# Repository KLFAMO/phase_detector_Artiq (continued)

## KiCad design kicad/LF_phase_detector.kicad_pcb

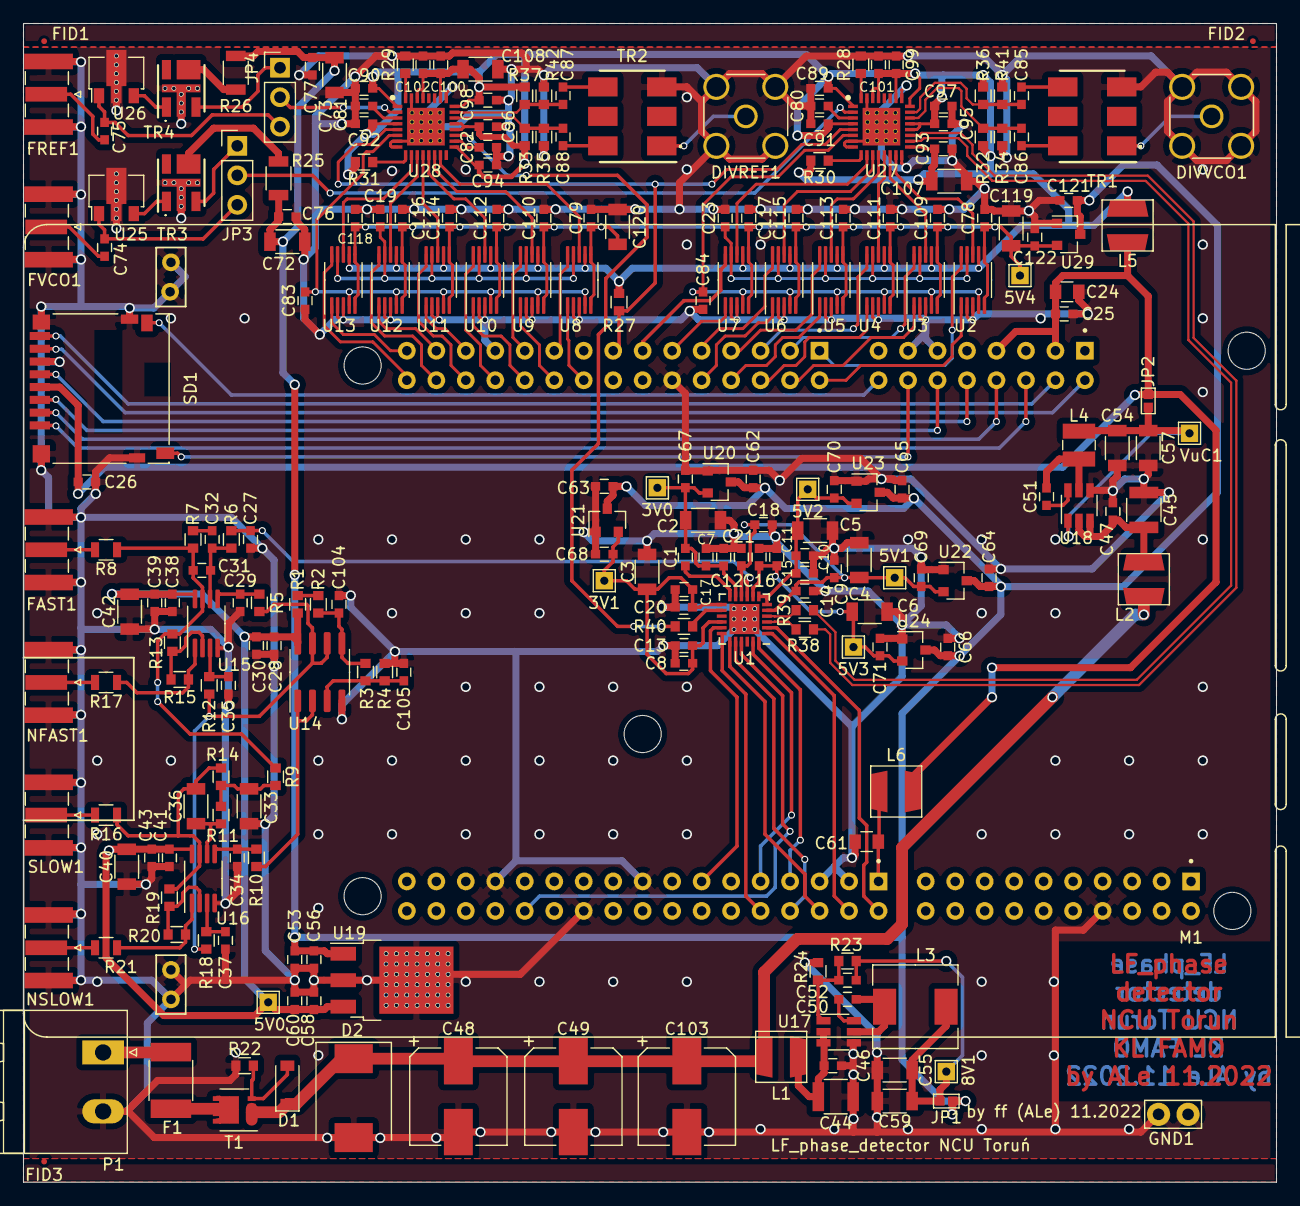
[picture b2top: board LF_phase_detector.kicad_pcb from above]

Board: 2 copper layers, 108.0 x 99.8 mm, 233 parts (0 on the bottom side), 143 nets.

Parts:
3V0, 3V1, 5V0, 5V1, 5V2, 5V3, 5V4, 8V1: TestPoint; Test_Point_THTPad_1.5x1.5mm_Drill0.7mm
C1, C12, C13, C14, C15, C16, C20, C21, C80, C81, C82: 1n 50V C0G; C_0603
C2, C3, C4, C5, C6, C40, C42, C72, C73, C107, C108, C119, C120: 10uF 25V X5R; C_1206
C7, C8, C9, C10, C11, C17, C18, C19, C23, C25, C26, C30, C39, C43, C46, C47, C50, C51, C56, C58, C76, C77, C78, C79, C83, C84, C89, C90, C91, C92, C93, C94, C95, C96, C97, C98, C99, C100, C101, C102, C109, C110, C111, C112, C113, C114, C115, C116, C117, C118: 100n 50V X7R; C_0603
C24, C61: GRM21BR71A106KE51L; C_0805
C27: 470p 50V C0G; C_0603
C28, C38, C41: 100p 50V C0G; C_0603
C29, C32, C34, C35, C37, C74, C75, C85, C86, C87, C88, C104, C105: 10n 50V C0G; C_0603
C31: DNP; C_0603
C33: 100n 50V C0G; C_1206
C36: 20n 50V C0G; C_1206
C44, C45: GRM32ER71H106KA12L; C_1210
C48, C49, C103: EXV107M035A9MAA; CP_Elec_8x10.5
C52: 82p 50V C0G; C_0603
C53, C60, C62, C63, C64, C65, C66, C67, C68, C69, C70, C71, C121, C122: 4u7 10V X5R; C_0603
C54, C55, C57, C59: GRM31CR71A226KE15L; C_1206
D1: BZT52C15; D_SOD-123
D2: SMAJ24A; D_SMC
DIVREF1: SMA6251A1-3GT50G-50; SMA_Amphenol_132291-12_Vertical
DIVVCO1: SMA6251A1-3GT50G-50; SMA_Amphenol_132291-12_Vertical
F1: 0ZCG0110CF2B; R_1812
FAST1: RF2-145A-T-17-50-G-HDW; SMA_Samtec_SMA-J-P-X-ST-EM1_EdgeMount
FID1, FID2, FID3: PAD; Fiducial_0.5mm_Dia_1mm_Outer
FREF1: RF2-145A-T-17-50-G-HDW; SMA_Samtec_SMA-J-P-X-ST-EM1_EdgeMount
FVCO1: RF2-145A-T-17-50-G-HDW; SMA_Samtec_SMA-J-P-X-ST-EM1_EdgeMount
GND1: TestPoint; Test_Point_Bridge_Pitch2.54mm_Drill1.0mm
JP1, JP2: Jumper_NO_Small; GS2_small
JP3, JP4: igły 3x1x2,54mm; Pin_Header_Straight_1x03_Pitch2.54mm
L1, L2: LQH44PH220MPRL; L_MURATA_LQH44
L3: 74477710; L_Wuerth_HCM-7050
L4: SRP3212-3R3M; L_Bourns_SRP3212
L5, L6: LQH44PN330MPRL; L_MURATA_LQH44
M1: NUCLEO-H743ZI; MODULE_NUCLEO-F746ZG_mini_M
NFAST1: RF2-145A-T-17-50-G-HDW; SMA_Samtec_SMA-J-P-X-ST-EM1_EdgeMount
NSLOW1: RF2-145A-T-17-50-G-HDW; SMA_Samtec_SMA-J-P-X-ST-EM1_EdgeMount
P1: MSTBA 2,5/ 2-G-5,08 - 1757242; PhoenixContact_MSTBA-G_02x5.08mm_Angled
R1, R2, R3, R4, R5, R10, R12, R13, R15, R18, R19, R20, R27, R30, R31: 10k 1%; R_0603_ff
R6, R7: 150R 1%; R_0603_ff
R8, R16, R17, R21: 49,9R 1%; R_0805
R9, R14: 1k 1%; R_0603_ff
R11: 2,26k 1%; R_0603_ff
R22: 4,7k; R_0603_ff
R23: 180k 1%; R_0603_ff
R24: 20k 1%; R_0603_ff
R25, R26: 133R 1%; R_1206
R28, R29: 4,12k 1%; R_0603_ff
R32, R33, R36, R37: 127R 1%; R_0603_ff
R34, R35, R41, R42: 83R 1%; R_0603_ff
R38, R39, R40: 24,9R 1%; R_0603_ff
SD1: DM3D-SF; Hirose_DM3D-SF
SLOW1: RF2-145A-T-17-50-G-HDW; SMA_Samtec_SMA-J-P-X-ST-EM1_EdgeMount
T1: AO4485; Diodes_PowerDI3333-8
TR1, TR2: ADT2-1T+; ADT21T1P
TR3, TR4: TCBT-14+; TCBT14
U1: HMC984LP4E; QFN-24_4x4mm_Pitch0.5mm_NoMask
U2, U3, U4, U5, U6, U7, U8, U9, U10, U11, U12, U13: TMUX1204DGSR; VSSOP-10_3x3mm_P0.5mm
U14: OPA2325; SOIC-8_3.9x4.9mm_P1.27mm
U15, U16: ADA4807-2ARM; MSOP-8_3x3mm_P0.65mm
U17: AP63200WU; TSOT-23-6
U18: AP63203WU-7; TSOT-23-6
U19: L78M05ACDT; TO-252-3_TabPin2
U20, U21: AP2210N-3.0TRG1; SOT-23
U22, U23, U24, U29: AP2210N-5.0TRG1; SOT-23
U25, U26: GALI-39+; SOT-89-3
U27, U28: AD9515BCPZ; QFN-32-1EP_5x5mm_Pitch0.5mm_ThermalVias
VuC1: TestPoint; Test_Point_THTPad_1.5x1.5mm_Drill0.7mm

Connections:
+3V3: C89.1, C90.1, C91.1, C92.1, C93.1, C94.1, C95.1, C96.1, C97.1, C98.1, C99.1, C100.1, C101.1, C102.1, C107.1, C108.1, L5.1, R27.2, R30.2, R31.2, R32.2, R33.2, R36.2, R37.2, U2.7, U3.7, U4.7, U5.7, U6.7, U7.7, U8.7, U9.7, U10.7, U11.7, U12.7, U13.7, U27.1, U27.4, U27.17, U27.20, U27.21, U27.24, U27.26, U27.29, U27.30, U28.1, U28.4, U28.17, U28.20, U28.21, U28.24, U28.26, U28.29, U28.30
+5V: 5V4.1, C78.1, C79.1, C109.1, C110.1, C111.1, C112.1, C113.1, C114.1, C115.1, C116.1, C117.1, C118.1, C119.1, C120.1, C122.1, U2.5, U2.6, U3.5, U3.6, U4.5, U4.6, U5.5, U5.6, U6.5, U6.6, U7.5, U7.6, U8.5, U8.6, U9.5, U9.6, U10.5, U10.6, U11.5, U11.6, U12.5, U12.6, U13.5, U13.6, U29.2
+5VA: 5V0.1, C28.1, C30.1, C38.1, C39.1, C40.2, C41.1, C42.1, C43.1, C58.2, C60.1, R1.2, U14.8, U15.8, U16.8, U19.3
+8V: C53.1, C56.2, C62.1, C63.1, C64.1, C65.1, C66.1, C72.1, C73.1, C76.1, C77.1, C121.1, JP1.2, R25.1, R26.1, U19.1, U20.3, U21.3, U22.3, U23.3, U24.3, U29.3
+15V: C48.1, C49.1, C103.1, D1.1, D2.1, L1.2, L2.2, T1.1, T1.2, T1.3
/Inputs and prescaler/DIV10+: C85.1, R36.1, R41.1, U27.23
/Inputs and prescaler/DIV10-: C86.1, R32.1, R34.1, U27.22
/Inputs and prescaler/DIV11+: R38.1, U27.19
/Inputs and prescaler/DIV11-: R39.1, U27.18
/Inputs and prescaler/DIV20+: C87.1, R37.1, R42.1, U28.23
/Inputs and prescaler/DIV20-: C88.1, R33.1, R35.1, U28.22
/Loop filter and outputs/VHALF: R5.1, R12.1, R18.1, U14.6, U14.7
/Loop filter and outputs/VQUOTER: R10.1, U14.1, U14.2
/Microcontroller F030/AS1_2: M1.CN9_2, U2.1
/Microcontroller F030/AS1_3: M1.CN9_4, U3.1
/Microcontroller F030/AS1_4: M1.CN9_6, U4.1
/Microcontroller F030/AS1_5: M1.CN9_8, U5.1
/Microcontroller F030/AS1_6: M1.CN9_10, U6.1
/Microcontroller F030/AS1_7: M1.CN9_11, U7.1
/Microcontroller F030/AS2_2: M1.CN9_18, U8.1
/Microcontroller F030/AS2_3: M1.CN9_20, U9.1
/Microcontroller F030/AS2_4: M1.CN9_22, U10.1
/Microcontroller F030/AS2_5: M1.CN9_25, U11.1
/Microcontroller F030/AS2_6: M1.CN9_27, U12.1
/Microcontroller F030/AS2_7: M1.CN9_29, U13.1
/Microcontroller F030/BS1_2: M1.CN9_1, U2.10
/Microcontroller F030/BS1_3: M1.CN9_3, U3.10
/Microcontroller F030/BS1_4: M1.CN9_5, U4.10
/Microcontroller F030/BS1_5: M1.CN9_7, U5.10
/Microcontroller F030/BS1_6: M1.CN9_9, U6.10
/Microcontroller F030/BS1_7: M1.CN9_13, U7.10
/Microcontroller F030/BS2_2: M1.CN9_19, U8.10
/Microcontroller F030/BS2_3: M1.CN9_21, U9.10
/Microcontroller F030/BS2_4: M1.CN9_24, U10.10
/Microcontroller F030/BS2_5: M1.CN9_26, U11.10
/Microcontroller F030/BS2_6: M1.CN9_28, U12.10
/Microcontroller F030/BS2_7: M1.CN9_30, U13.10
/Microcontroller F030/REF1_1:3: C23.1, U2.9, U3.9, U4.9, U5.9, U6.9, U7.9
/Microcontroller F030/REF2_1:3: C19.1, U8.9, U9.9, U10.9, U11.9, U12.9, U13.9
/Microcontroller F030/uC feed and SDcard/SD_CK: M1.CN8_10, SD1.5
/Microcontroller F030/uC feed and SDcard/SD_CMD: M1.CN8_12, SD1.3
/Microcontroller F030/uC feed and SDcard/SD_D0: M1.CN8_2, SD1.7
/Microcontroller F030/uC feed and SDcard/SD_D1: M1.CN8_4, SD1.8
/Microcontroller F030/uC feed and SDcard/SD_D2: M1.CN8_6, SD1.1
/Microcontroller F030/uC feed and SDcard/SD_D3: M1.CN8_8, SD1.2
/Microcontroller F030/uC feed and SDcard/SD_DET1: M1.CN8_16, SD1.9
/Microcontroller F030/uC feed and SDcard/SD_DET2: M1.CN8_14, SD1.10
AVDD: 3V0.1, C1.2, C2.1, C7.1, C12.1, C67.1, U1.11, U20.2
CEN: M1.CN10_13, U1.17
CP: C27.2, R6.2, U1.9
DIV1+: R38.2, U1.3
DIV1-: R39.2, U1.4
DIV2: R40.2, U1.14
DNSAT: M1.CN10_7, U1.24
DVDD: 3V1.1, C3.1, C8.1, C13.1, C17.1, C20.1, C68.1, U1.13, U1.16, U21.2
GND: C2.2, C3.2, C4.2, C5.2, C6.2, C7.2, C8.2, C9.2, C10.2, C11.2, C12.2, C13.2, C14.2, C15.2, C16.2, C17.2, C18.2, C19.2, C20.2, C21.2, C23.2, C24.2, C25.2, C26.2, C27.1, C28.2, C29.2, C30.2, C33.2, C34.2, C35.2, C37.2, C38.2, C39.2, C40.1, C41.2, C42.2, C43.2, C44.2, C45.2, C46.2, C47.2, C48.2, C49.2, C53.2, C54.2, C55.2, C56.1, C57.2, C58.1, C59.2, C60.2, C61.2, C62.2, C63.2, C64.2, C65.2, C66.2, C67.2, C68.2, C69.2, C70.2, C71.2, C72.2, C73.2, C76.2, C77.2, C78.2, C79.2, C80.1, C81.1, C82.1, C83.2, C84.2, C89.2, C90.2, C91.2, C92.2, C93.2, C94.2, C95.2, C96.2, C97.2, C98.2, C99.2, C100.2, C101.2, C102.2, C103.2, C104.2, C105.2, C107.2, C108.2, C109.2, C110.2, C111.2, C112.2, C113.2, C114.2, C115.2, C116.2, C117.2, C118.2, C119.2, C120.2, C121.2, C122.2, D2.2, DIVREF1.2, DIVVCO1.2, FAST1.2, FREF1.2, FVCO1.2, GND1.1, M1.35, M1.CN7_8, M1.CN8_11, M1.CN8_13, M1.CN9_12, M1.CN9_23, M1.CN10_3, M1.CN10_5, M1.CN10_17, M1.CN10_22, M1.CN10_27, NFAST1.2, NSLOW1.2, P1.2, R4.1, R22.1, R24.2, R28.2, R29.2, R34.2, R35.2, R41.2, R42.2, SD1.6, SD1.11, SLOW1.2, TR1.3, TR2.3, TR3.5, TR4.5, U1.25, U2.2, U2.3, U3.2, U3.3, U4.2, U4.3, U5.2, U5.3, U6.2, U6.3, U7.2, U7.3, U8.2, U8.3, U9.2, U9.3, U10.2, U10.3, U11.2, U11.3, U12.2, U12.3, U13.2, U13.3, U14.4, U15.4, U16.4, U17.4, U18.4, U19.2, U20.1, U21.1, U22.1, U23.1, U24.1, U25.2, U26.2, U27.7, U27.8, U27.16, U27.25, U27.31, U27.33, U28.7, U28.8, U28.25, U28.31, U28.33, U29.1
LD-D0: M1.CN10_2, U1.2
MISO: M1.CN10_10, U1.18
MOSI: M1.CN10_8, U1.20
NSS: M1.CN10_6, U1.19
unnamed: 8V1.1, C52.1, C55.1, C59.1, JP1.1, L3.1, R23.1
unnamed: C1.1, U1.12
unnamed: C29.1, R5.2, U15.5
unnamed: C31.1, C32.1, R6.1, U15.6
unnamed: C31.2, R7.1, R8.1, R9.1, R13.1, U15.7
unnamed: C32.2, R7.2
unnamed: C33.1, R9.2, R11.2, R14.1
unnamed: C34.1, R10.2, U16.5
unnamed: C35.1, R12.2, U15.3
unnamed: C36.1, R11.1, U16.6
unnamed: C36.2, R14.2, R16.1, R19.1, U16.7
unnamed: C37.1, R18.2, U16.3
unnamed: C44.1, C46.1, L1.1, U17.2, U17.3
unnamed: C45.1, C47.1, L2.1, U18.2, U18.3
unnamed: C50.1, L3.2, U17.5
unnamed: C50.2, U17.6
unnamed: C51.1, L4.2, U18.5
unnamed: C51.2, U18.6
unnamed: C52.2, R23.2, R24.1, U17.1
unnamed: C54.1, C57.1, JP2.2, L4.1, U18.1, VuC1.1
unnamed: C74.1, JP3.3, U25.1
unnamed: C74.2, FVCO1.1
unnamed: C75.1, JP4.3, U26.1
unnamed: C75.2, FREF1.1
unnamed: C80.2, U27.3
unnamed: C81.2, U28.3
unnamed: C82.2, U28.18
unnamed: C85.2, TR1.4
unnamed: C86.2, TR1.6
unnamed: C87.2, TR2.4
unnamed: C88.2, TR2.6
unnamed: C104.1, R2.1, R3.2, U14.5
unnamed: C105.1, R3.1, R4.2, U14.3
unnamed: D1.2, R22.2, T1.4
unnamed: DIVREF1.1, TR2.1
unnamed: DIVVCO1.1, TR1.1
unnamed: F1.1, T1.5
unnamed: F1.2, P1.1
unnamed: FAST1.1, R8.2
unnamed: JP3.1, TR3.2
unnamed: JP3.2, U27.2
unnamed: JP4.1, TR4.2
unnamed: JP4.2, U28.2
unnamed: NFAST1.1, R17.2
unnamed: NSLOW1.1, R21.2
unnamed: R1.1, R2.2
unnamed: R13.2, R15.1, U15.2
unnamed: R15.2, R17.1, U15.1
unnamed: R16.2, SLOW1.1
unnamed: R19.2, R20.1, U16.2
unnamed: R20.2, R21.1, U16.1
unnamed: R25.2, TR3.3
unnamed: R26.2, TR4.3
unnamed: R28.1, U27.32
unnamed: R29.1, U28.32
unnamed: R30.1, U27.9
unnamed: R31.1, U28.9
unnamed: R40.1, U28.19
unnamed: TR3.1, U25.3
unnamed: TR4.1, U26.3
REF123: C84.1, U2.4, U3.4, U4.4, U5.4, U6.4, U7.4, U27.6
REF223: C83.1, U8.4, U9.4, U10.4, U11.4, U12.4, U13.4, U28.6
REFEN: M1.CN10_4, U1.1
S1_2: U2.8, U27.15
S1_3: U3.8, U27.14
S1_4: U4.8, U27.13
S1_5: U5.8, U27.12
S1_6: U6.8, U27.11
S1_7: U7.8, U27.10
S2_2: U8.8, U28.15
S2_3: U9.8, U28.14
S2_4: U10.8, U28.13
S2_5: U11.8, U28.12
S2_6: U12.8, U28.11
S2_7: U13.8, U28.10
SCK: M1.CN10_26, U1.21
SYNCB: M1.CN9_15, R27.1, U27.5, U28.5
UPSAT: M1.CN10_9, U1.23
VAREF: C61.1, L6.1, M1.CN10_1
VCCPD: 5V1.1, C4.1, C9.1, C14.1, C18.1, C21.1, C69.1, U1.5, U1.10, U22.2
VDDCP: 5V3.1, C6.1, C11.1, C16.1, C71.1, U1.8, U24.2
VDDPD: 5V2.1, C5.1, C10.1, C15.1, C70.1, U1.6, U1.7, U23.2
VuC: C24.1, C25.1, C26.1, JP2.1, L5.2, L6.2, M1.CN8_3, M1.CN8_7, SD1.4

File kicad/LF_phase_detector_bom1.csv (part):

"Source:","D:\Projekty\FAMO\LF_phase_detector\LF_phase_detector.sch"
"Date:","24.11.2022 08:50:30"
"Tool:","Eeschema (5.1.12)-1"
"Generator:","C:\Program Files\KiCad\bin\scripting\plugins/bom_csv_grouped_by_value.py"
"Component Count:","233"

"Individual Components:"

"Item","Qty","Reference(s)","Value","LibPart","Footprint","Datasheet","Comm","Vendor"
"","","3V0","TestPoint","Connector:TestPoint","Connectors_TestPoints:Test_Point_THTPad_1.5x1.5mm_Drill0.7mm","~","",""
"","","3V1","TestPoint","Connector:TestPoint","Connectors_TestPoints:Test_Point_THTPad_1.5x1.5mm_Drill0.7mm","~","",""
"","","5V0","TestPoint","Connector:TestPoint","Connectors_TestPoints:Test_Point_THTPad_1.5x1.5mm_Drill0.7mm","~","",""
"","","5V1","TestPoint","Connector:TestPoint","Connectors_TestPoints:Test_Point_THTPad_1.5x1.5mm_Drill0.7mm","~","",""
"","","5V2","TestPoint","Connector:TestPoint","Connectors_TestPoints:Test_Point_THTPad_1.5x1.5mm_Drill0.7mm","~","",""
"","","5V3","TestPoint","Connector:TestPoint","Connectors_TestPoints:Test_Point_THTPad_1.5x1.5mm_Drill0.7mm","~","",""
"","","5V4","TestPoint","Connector:TestPoint","Connectors_TestPoints:Test_Point_THTPad_1.5x1.5mm_Drill0.7mm","~","",""
"","","8V1","TestPoint","Connector:TestPoint","Connectors_TestPoints:Test_Point_THTPad_1.5x1.5mm_Drill0.7mm","~","",""
"","","C1","1n 50V C0G","Device:C","Capacitors_SMD:C_0603","~","",""
"","","C2","10uF 25V X5R","Device:C","Capacitors_SMD:C_1206","~","",""
"","","C3","10uF 25V X5R","Device:C","Capacitors_SMD:C_1206","~","",""
"","","C4","10uF 25V X5R","Device:C","Capacitors_SMD:C_1206","~","",""
"","","C5","10uF 25V X5R","Device:C","Capacitors_SMD:C_1206","~","",""
"","","C6","10uF 25V X5R","Device:C","Capacitors_SMD:C_1206","~","",""
"","","C7","100n 50V X7R","Device:C","Capacitors_SMD:C_0603","~","",""
"","","C8","100n 50V X7R","Device:C","Capacitors_SMD:C_0603","~","",""
"","","C9","100n 50V X7R","Device:C","Capacitors_SMD:C_0603","~","",""
"","","C10","100n 50V X7R","Device:C","Capacitors_SMD:C_0603","~","",""
"","","C11","100n 50V X7R","Device:C","Capacitors_SMD:C_0603","~","",""
"","","C12","1n 50V C0G","Device:C","Capacitors_SMD:C_0603","~","",""
"","","C13","1n 50V C0G","Device:C","Capacitors_SMD:C_0603","~","",""
"","","C14","1n 50V C0G","Device:C","Capacitors_SMD:C_0603","~","",""
"","","C15","1n 50V C0G","Device:C","Capacitors_SMD:C_0603","~","",""
"","","C16","1n 50V C0G","Device:C","Capacitors_SMD:C_0603","~","",""
"","","C17","100n 50V X7R","Device:C","Capacitors_SMD:C_0603","~","",""
"","","C18","100n 50V X7R","Device:C","Capacitors_SMD:C_0603","~","",""
"","","C19","100n 50V X7R","Device:C","Capacitors_SMD:C_0603","~","",""
"","","C20","1n 50V C0G","Device:C","Capacitors_SMD:C_0603","~","",""
"","","C21","1n 50V C0G","Device:C","Capacitors_SMD:C_0603","~","",""
"","","C23","100n 50V X7R","Device:C","Capacitors_SMD:C_0603","~","",""
"","","C24","10u X7R 50V","Device:C","Capacitors_SMD:C_1210","~","",""
"","","C25","100n X7R 50V","Device:C","Capacitors_SMD:C_0603","~","",""
"","","C26","100n X7R 50V","Device:C","Capacitors_SMD:C_0603","~","",""
"","","C27","470p 50V C0G","Device:C","Capacitors_SMD:C_0603","~","",""
"","","C28","100p 50V C0G","Device:C","Capacitors_SMD:C_0603","~","",""
"","","C29","10n 50V C0G","Device:C","Capacitors_SMD:C_0603","~","",""
"","","C30","100n 50V X7R","Device:C","Capacitors_SMD:C_0603","~","",""
"","","C31","DNP","Device:C","Capacitors_SMD:C_0603","~","(470p 50V C0G)",""
"","","C32","10n 50V C0G","Device:C","Capacitors_SMD:C_0603","~","",""
"","","C33","100n 50V C0G","Device:C","Capacitors_SMD:C_1206","~","",""
"","","C34","10n 50V C0G","Device:C","Capacitors_SMD:C_0603","~","",""
"","","C35","10n 50V C0G","Device:C","Capacitors_SMD:C_0603","~","",""
"","","C36","20n 50V C0G","Device:C","Capacitors_SMD:C_1206","~","",""
"","","C37","10n 50V C0G","Device:C","Capacitors_SMD:C_0603","~","",""
"","","C38","100p 50V C0G","Device:C","Capacitors_SMD:C_0603","~","",""
"","","C39","100n 50V X7R","Device:C","Capacitors_SMD:C_0603","~","",""
"","","C40","10uF 25V X5R","Device:C","Capacitors_SMD:C_1206","~","",""
"","","C41","100p 50V C0G","Device:C","Capacitors_SMD:C_0603","~","",""
"","","C42","10uF 25V X5R","Device:C","Capacitors_SMD:C_1206","~","",""
"","","C43","100n 50V X7R","Device:C","Capacitors_SMD:C_0603","~","",""
"","","C44","GRM32ER71H106KA12L","Device:C","Capacitors_SMD:C_1210","~","10u 50V X7R Murata",""
"","","C45","GRM32ER71H106KA12L","Device:C","Capacitors_SMD:C_1210","~","10u 50V X7R Murata",""
"","","C46","100n 50V X7R","Device:C","Capacitors_SMD:C_0603","~","",""
"","","C47","100n 50V X7R","Device:C","Capacitors_SMD:C_0603","~","",""
"","","C48","EXV107M035A9MAA","Device:CP","Capacitors_SMD:CP_Elec_8x10.5","~","≥100u ≥30V ≥4000h Ø8 ≥105°C ",""
"","","C49","EXV107M035A9MAA","Device:CP","Capacitors_SMD:CP_Elec_8x10.5","~","≥100u ≥30V ≥4000h Ø8 ≥105°C ",""
"","","C50","100n 50V X7R","Device:C","Capacitors_SMD:C_0603","~","",""
"","","C51","100n 50V X7R","Device:C","Capacitors_SMD:C_0603","~","",""
"","","C52","82p 50V C0G","Device:C","Capacitors_SMD:C_0603","~","",""
"","","C53","4u7 X5R 10V","Device:C","Capacitors_SMD:C_0603","~","",""
"","","C54","GRM31CR71A226KE15L","Device:C","Capacitors_SMD:C_1206","~","22u 10V X7R Murata",""
"","","C55","GRM31CR71A226KE15L","Device:C","Capacitors_SMD:C_1206","~","22u 10V X7R Murata",""
"","","C56","100n 50V X7R","Device:C","Capacitors_SMD:C_0603","~","",""
"","","C57","GRM31CR71A226KE15L","Device:C","Capacitors_SMD:C_1206","~","22u 10V X7R Murata",""
"","","C58","100n 50V X7R","Device:C","Capacitors_SMD:C_0603","~","",""
"","","C59","GRM31CR71A226KE15L","Device:C","Capacitors_SMD:C_1206","~","22u 10V X7R Murata",""
"","","C60","4u7 X5R 10V","Device:C","Capacitors_SMD:C_0603","~","",""
"","","C61","GRM21BR71A106KE51L","Device:C","Capacitors_SMD:C_0805","~","10u 10V X7R",""
"","","C62","4u7 X5R 10V","Device:C","Capacitors_SMD:C_0603","~","",""
"","","C63","4u7 X5R 10V","Device:C","Capacitors_SMD:C_0603","~","",""
"","","C64","4u7 X5R 10V","Device:C","Capacitors_SMD:C_0603","~","",""
"","","C65","4u7 X5R 10V","Device:C","Capacitors_SMD:C_0603","~","",""
"","","C66","4u7 X5R 10V","Device:C","Capacitors_SMD:C_0603","~","",""
"","","C67","4u7 X5R 10V","Device:C","Capacitors_SMD:C_0603","~","",""
"","","C68","4u7 X5R 10V","Device:C","Capacitors_SMD:C_0603","~","",""
"","","C69","4u7 X5R 10V","Device:C","Capacitors_SMD:C_0603","~","",""
"","","C70","4u7 X5R 10V","Device:C","Capacitors_SMD:C_0603","~","",""
"","","C71","4u7 X5R 10V","Device:C","Capacitors_SMD:C_0603","~","",""
"","","C72","10uF 25V X5R","Device:C","Capacitors_SMD:C_1206","~","",""
"","","C73","10uF 25V X5R","Device:C","Capacitors_SMD:C_1206","~","",""
"","","C74","10n 50V C0G","Device:C","Capacitors_SMD:C_0603","~","",""
"","","C75","10n 50V C0G","Device:C","Capacitors_SMD:C_0603","~","",""
"","","C76","100n 50V X7R","Device:C","Capacitors_SMD:C_0603","~","",""
"","","C77","100n 50V X7R","Device:C","Capacitors_SMD:C_0603","~","",""
"","","C78","100n 50V X7R","Device:C","Capacitors_SMD:C_0603","~","",""
"","","C79","100n 50V X7R","Device:C","Capacitors_SMD:C_0603","~","",""
"","","C80","1n 50V C0G","Device:C","Capacitors_SMD:C_0603","~","",""
"","","C81","1n 50V C0G","Device:C","Capacitors_SMD:C_0603","~","",""
"","","C82","1n 50V C0G","Device:C","Capacitors_SMD:C_0603","~","",""
"","","C83","100n 50V X7R","Device:C","Capacitors_SMD:C_0603","~","",""
"","","C84","100n 50V X7R","Device:C","Capacitors_SMD:C_0603","~","",""
"","","C85","10n 50V C0G","Device:C","Capacitors_SMD:C_0603","~","",""
"","","C86","10n 50V C0G","Device:C","Capacitors_SMD:C_0603","~","",""
"","","C87","10n 50V C0G","Device:C","Capacitors_SMD:C_0603","~","",""
"","","C88","10n 50V C0G","Device:C","Capacitors_SMD:C_0603","~","",""
"","","C89","100n 50V X7R","Device:C","Capacitors_SMD:C_0603","~","",""
"","","C90","100n 50V X7R","Device:C","Capacitors_SMD:C_0603","~","",""
"","","C91","100n 50V X7R","Device:C","Capacitors_SMD:C_0603","~","",""
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
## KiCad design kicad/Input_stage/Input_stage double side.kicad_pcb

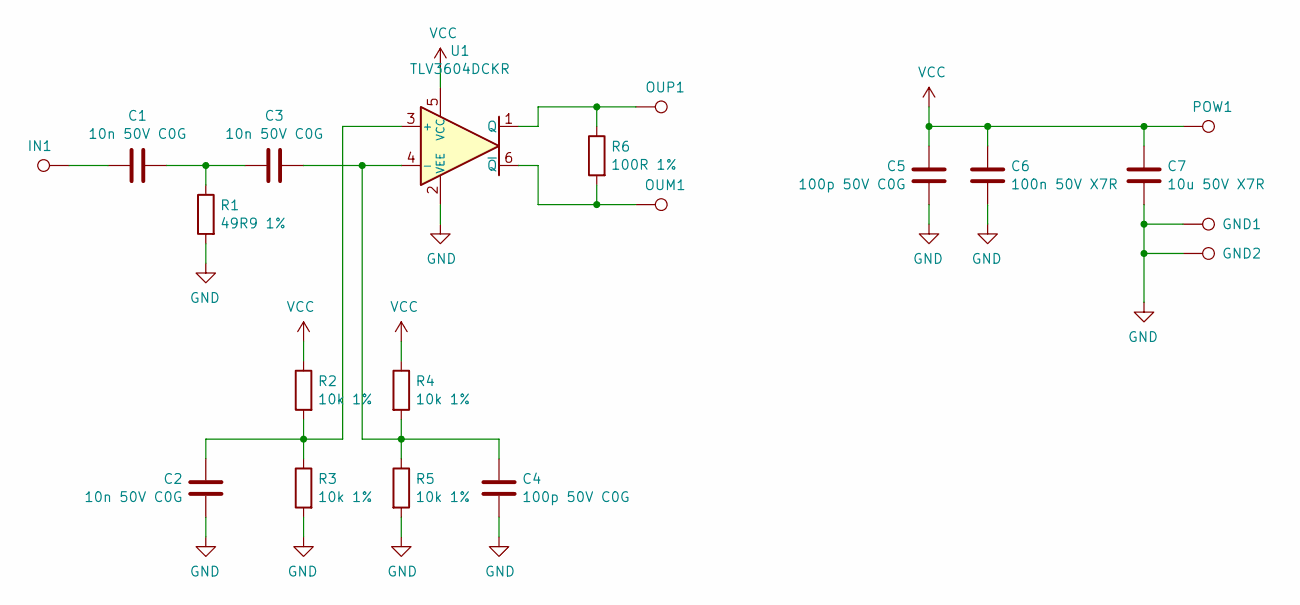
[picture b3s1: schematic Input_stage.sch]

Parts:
C1, C2, C3: 10n 50V C0G; C_0603
C4, C5: 100p 50V C0G; C_0603
C6: 100n 50V X7R; C_0603
C7: 10u 50V X7R; C_1206
GND1, GND2: TestPoint; Test_Point_THTPad_d1.5mm_Drill0.7mm
IN1: TestPoint; Test_Point_THTPad_d1.5mm_Drill0.7mm
OUM1: TestPoint; Test_Point_THTPad_d1.5mm_Drill0.7mm
OUP1: TestPoint; Test_Point_THTPad_d1.5mm_Drill0.7mm
POW1: TestPoint; Test_Point_THTPad_d1.5mm_Drill0.7mm
R1: 49R9 1%; R_0603_ff
R2, R3, R4, R5: 10k 1%; R_0603_ff
R6: 100R 1%; R_0603_ff
U1: TLV3604DCKR; SOT-363_SC-70-6

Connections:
GND: C2.2, C4.2, C5.2, C6.2, C7.2, GND1.1, GND2.1, R1.2, R3.2, R5.2, U1.2 (VEE); also elsewhere on the board
unnamed: C1.1, C3.2, R1.1
unnamed: C1.2, IN1.1
unnamed: C2.1, R2.2, R3.1, U1.3 (+)
unnamed: C3.1, C4.1, R4.2, R5.1, U1.4 (-)
unnamed: OUM1.1, R6.2, U1.6 (~Q)
unnamed: OUP1.1, R6.1, U1.1 (Q)
VCC: C5.1, C6.1, C7.1, POW1.1, R2.1, R4.1, U1.5 (VCC)

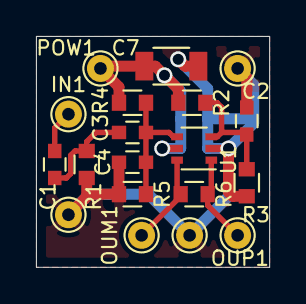
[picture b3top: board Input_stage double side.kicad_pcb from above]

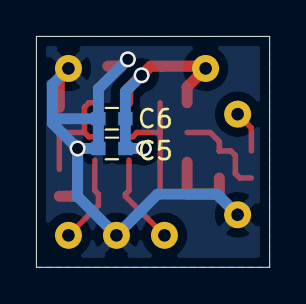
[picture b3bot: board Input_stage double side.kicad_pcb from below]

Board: 2 copper layers, 13.0 x 12.8 mm, 21 parts (2 on the bottom side), 8 nets.

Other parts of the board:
GND3: TestPoint; Test_Point_THTPad_d1.5mm_Drill0.7mm

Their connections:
GND: GND3.1; also elsewhere on the board

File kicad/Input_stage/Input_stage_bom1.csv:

"Source:","D:\Projekty\FAMO\LF_phase_detector\Input_stage\Input_stage.sch"
"Date:","20.07.2023 13:49:09"
"Tool:","Eeschema (5.1.12)-1"
"Generator:","C:\Program Files\KiCad\bin\scripting\plugins/bom_csv_grouped_by_value.py"
"Component Count:","20"

"Individual Components:"

"Item","Qty","Reference(s)","Value","LibPart","Footprint","Datasheet"
"","","C1","10n 50V C0G","Device:C","Capacitors_SMD:C_0603","~"
"","","C2","10n 50V C0G","Device:C","Capacitors_SMD:C_0603","~"
"","","C3","10n 50V C0G","Device:C","Capacitors_SMD:C_0603","~"
"","","C4","100p 50V C0G","Device:C","Capacitors_SMD:C_0603","~"
"","","C5","100p 50V C0G","Device:C","Capacitors_SMD:C_0603","~"
"","","C6","100n 50V X7R","Device:C","Capacitors_SMD:C_0603","~"
"","","C7","10u 50V X7R","Device:C","Capacitors_SMD:C_1206","~"
"","","GND1","TestPoint","Connector:TestPoint","Connectors_TestPoints:Test_Point_THTPad_d1.5mm_Drill0.7mm","~"
"","","GND2","TestPoint","Connector:TestPoint","Connectors_TestPoints:Test_Point_THTPad_d1.5mm_Drill0.7mm","~"
"","","IN1","TestPoint","Connector:TestPoint","Connectors_TestPoints:Test_Point_THTPad_d1.5mm_Drill0.7mm","~"
"","","OUM1","TestPoint","Connector:TestPoint","Connectors_TestPoints:Test_Point_THTPad_d1.5mm_Drill0.7mm","~"
"","","OUP1","TestPoint","Connector:TestPoint","Connectors_TestPoints:Test_Point_THTPad_d1.5mm_Drill0.7mm","~"
"","","POW1","TestPoint","Connector:TestPoint","Connectors_TestPoints:Test_Point_THTPad_d1.5mm_Drill0.7mm","~"
"","","R1","49R9 1%","Device:R","ff_lib:R_0603_ff","~"
"","","R2","10k 1%","Device:R","ff_lib:R_0603_ff","~"
"","","R3","10k 1%","Device:R","ff_lib:R_0603_ff","~"
"","","R4","10k 1%","Device:R","ff_lib:R_0603_ff","~"
"","","R5","10k 1%","Device:R","ff_lib:R_0603_ff","~"
"","","R6","100R 1%","Device:R","ff_lib:R_0603_ff","~"
"","","U1","TLV3604DCKR","Comparator:LTC6754xSC6","Package_TO_SOT_SMD:SOT-363_SC-70-6","https://www.ti.com/lit/ds/symlink/tlv3604.pdf?ts=16895963084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"



"Collated Components:"

"Item","Qty","Reference(s)","Value","LibPart","Footprint","Datasheet"
"1","3","C1, C2, C3","10n 50V C0G","Device:C","Capacitors_SMD:C_0603","~"
"2","2","C4, C5","100p 50V C0G","Device:C","Capacitors_SMD:C_0603","~"
"3","1","C6","100n 50V X7R","Device:C","Capacitors_SMD:C_0603","~"
"4","1","C7","10u 50V X7R","Device:C","Capacitors_SMD:C_1206","~"
"5","6","GND1, GND2, IN1, OUM1, OUP1, POW1","TestPoint","Connector:TestPoint","Connectors_TestPoints:Test_Point_THTPad_d1.5mm_Drill0.7mm","~"
"6","1","R1","49R9 1%","Device:R","ff_lib:R_0603_ff","~"
"7","4","R2, R3, R4, R5","10k 1%","Device:R","ff_lib:R_0603_ff","~"
"8","1","R6","100R 1%","Device:R","ff_lib:R_0603_ff","~"
"9","1","U1","TLV3604DCKR","Comparator:LTC6754xSC6","Package_TO_SOT_SMD:SOT-363_SC-70-6","https://www.ti.com/lit/ds/symlink/tlv3604.pdf?ts=16895963084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"

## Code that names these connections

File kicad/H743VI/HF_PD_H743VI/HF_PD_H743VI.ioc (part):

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Mcu.Name=STM32H743VITx
Mcu.Package=LQFP100
Mcu.UserName=STM32H743VITx
PA0.GPIOParameters=GPIO_Label
PA0.GPIO_Label=XREF
PA0.Signal=S_TIM2_CH1_ETR
PA1.GPIOParameters=GPIO_Label
PA1.GPIO_Label=NSS_OUT
PA1.Signal=GPIO_Output
PA10.GPIOParameters=GPIO_PuPd,GPIO_Label
PA10.GPIO_Label=DIV1_2
PA10.GPIO_PuPd=GPIO_PULLUP
PA10.Signal=GPIO_Input
PA11.Mode=Asynchronous
PA11.Signal=UART4_RX
PA12.Mode=Asynchronous
PA12.Signal=UART4_TX
PA13\ (JTMS/SWDIO).Mode=JTAG_4_pins
PA13\ (JTMS/SWDIO).Signal=DEBUG_JTMS-SWDIO
PA14\ (JTCK/SWCLK).Mode=JTAG_4_pins
PA14\ (JTCK/SWCLK).Signal=DEBUG_JTCK-SWCLK
PA15\ (JTDI).Mode=JTAG_4_pins
PA15\ (JTDI).Signal=DEBUG_JTDI
PA2.GPIOParameters=PinState,GPIO_Label
PA2.GPIO_Label=MISO_OUT
PA2.PinState=GPIO_PIN_SET
PA2.Signal=GPIO_Output
PA3.GPIOParameters=GPIO_Label
PA3.GPIO_Label=MOSI_OUT
PA3.Signal=GPIO_Output
PA4.GPIOParameters=GPIO_Label
PA4.GPIO_Label=XVCO
PA4.Signal=S_TIM5_ETR
PA5.GPIOParameters=GPIO_Label
PA5.GPIO_Label=DAC_SCK
PA5.Mode=TX_Only_Simplex_Unidirect_Master
PA5.Signal=SPI1_SCK
PA6.GPIOParameters=PinState,GPIO_Label
PA6.GPIO_Label=DAC_NSS
PA6.PinState=GPIO_PIN_SET
PA6.Signal=GPIO_Output
PA7.GPIOParameters=GPIO_Label
PA7.GPIO_Label=DAC_MOSI
PA7.Mode=TX_Only_Simplex_Unidirect_Master
PA7.Signal=SPI1_MOSI
PA8.GPIOParameters=GPIO_PuPd,GPIO_Label
PA8.GPIO_Label=DIV1_8
PA8.GPIO_PuPd=GPIO_PULLUP
PA8.Signal=GPIO_Input
PA9.GPIOParameters=GPIO_PuPd,GPIO_Label
PA9.GPIO_Label=DIV1_4
PA9.GPIO_PuPd=GPIO_PULLUP
PA9.Signal=GPIO_Input
PB0.GPIOParameters=GPIO_Label
PB0.GPIO_Label=PD_ADC
PB0.Signal=ADCx_INP9
PB10.GPIOParameters=GPIO_Label
PB10.GPIO_Label=EEP_SCL
PB10.Mode=I2C
PB10.Signal=I2C2_SCL
PB11.GPIOParameters=GPIO_Label
PB11.GPIO_Label=EEP_SDA
PB11.Mode=I2C
PB11.Signal=I2C2_SDA
PB12.GPIOParameters=GPIO_Label
PB12.GPIO_Label=H984_NSS
PB12.Mode=NSS_Signal_Hard_Output
PB12.Signal=SPI2_NSS
PB13.GPIOParameters=GPIO_Label
PB13.GPIO_Label=H984_SCK
PB13.Mode=Full_Duplex_Master
PB13.Signal=SPI2_SCK
PB14.GPIOParameters=GPIO_Label
PB14.GPIO_Label=DNSAT
PB14.Signal=GPIO_Input
PB15.GPIOParameters=GPIO_Label
PB15.GPIO_Label=LD-DO
PB15.Signal=GPIO_Input
PB2.GPIOParameters=GPIO_Label
PB2.GPIO_Label=LED_MOSI
PB2.Mode=Full_Duplex_Master
PB2.Signal=SPI3_MOSI
PB3\ (JTDO/TRACESWO).Mode=JTAG_4_pins
PB3\ (JTDO/TRACESWO).Signal=DEBUG_JTDO-SWO
PB4\ (NJTRST).GPIOParameters=GPIO_Label
PB4\ (NJTRST).GPIO_Label=TTL6
PB4\ (NJTRST).Signal=GPIO_Output
PB5.GPIOParameters=GPIO_Label
PB5.GPIO_Label=TTL7
PB5.Signal=GPIO_Output
PB6.GPIOParameters=GPIO_Label
PB6.GPIO_Label=DAT6_OUT
PB6.Signal=GPIO_Output
PB9.GPIOParameters=GPIO_Label
PB9.GPIO_Label=DAT6
PB9.Signal=GPIO_Input
PC0.GPIOParameters=GPIO_Label
PC0.GPIO_Label=DAT4_OUT
PC0.Signal=GPIO_Output
PC1.GPIOParameters=GPIO_Label
PC1.GPIO_Label=H984_MOSI
PC1.Mode=Full_Duplex_Master
PC1.Signal=SPI2_MOSI
PC10.GPIOParameters=GPIO_Label
PC10.GPIO_Label=LED_SCK
PC10.Mode=Full_Duplex_Master
PC10.Signal=SPI3_SCK
PC11.GPIOParameters=GPIO_Label
PC11.GPIO_Label=LED_MISO
PC11.Mode=Full_Duplex_Master
PC11.Signal=SPI3_MISO
PC14-OSC32_IN\ (OSC32_IN).GPIOParameters=GPIO_Label
PC14-OSC32_IN\ (OSC32_IN).GPIO_Label=DAT5
PC14-OSC32_IN\ (OSC32_IN).Signal=GPIO_Input
PC15-OSC32_OUT\ (OSC32_OUT).GPIOParameters=GPIO_Label
PC15-OSC32_OUT\ (OSC32_OUT).GPIO_Label=DAT4
PC15-OSC32_OUT\ (OSC32_OUT).Signal=GPIO_Input
PC2_C.GPIOParameters=GPIO_Label
PC2_C.GPIO_Label=H984_MISO
PC2_C.Mode=Full_Duplex_Master
PC2_C.Signal=SPI2_MISO
PC3_C.GPIOParameters=GPIO_Label
PC3_C.GPIO_Label=DAT5_OUT
PC3_C.Signal=GPIO_Output
PC6.GPIOParameters=GPIO_PuPd,GPIO_Label
PC6.GPIO_Label=DIV2_8
PC6.GPIO_PuPd=GPIO_PULLUP
PC6.Signal=GPIO_Input
PC7.GPIOParameters=GPIO_PuPd,GPIO_Label
PC7.GPIO_Label=DIV2_4
PC7.GPIO_PuPd=GPIO_PULLUP
PC7.Signal=GPIO_Input
PC8.GPIOParameters=GPIO_PuPd,GPIO_Label
PC8.GPIO_Label=DIV2_2
PC8.GPIO_PuPd=GPIO_PULLUP
PC8.Signal=GPIO_Input
PC9.GPIOParameters=GPIO_PuPd,GPIO_Label
PC9.GPIO_Label=DIV1_16
PC9.GPIO_PuPd=GPIO_PULLUP
PC9.Signal=GPIO_Input
PD10.GPIOParameters=GPIO_Label
PD10.GPIO_Label=REFEN
PD10.Signal=GPXTI10
PD11.GPIOParameters=PinState,GPIO_Label
PD11.GPIO_Label=LED_NSS
PD11.PinState=GPIO_PIN_SET
PD11.Signal=GPIO_Output
PD12.GPIOParameters=GPIO_Label
PD12.GPIO_Label=LED_SCL
PD12.Mode=I2C
PD12.Signal=I2C4_SCL
PD13.GPIOParameters=GPIO_Label
PD13.GPIO_Label=LED_SDA
PD13.Mode=I2C
PD13.Signal=I2C4_SDA
PD14.GPIOParameters=GPIO_Label
PD14.GPIO_Label=LINK
PD14.Signal=GPXTI14
PD15.GPIOParameters=GPIO_PuPd,GPIO_Label
PD15.GPIO_Label=DIV2_16
PD15.GPIO_PuPd=GPIO_PULLUP
PD15.Signal=GPIO_Input
PD2.GPIOParameters=GPIO_Label
PD2.GPIO_Label=TTL0
PD2.Signal=GPXTI2
PD3.GPIOParameters=GPIO_Label
PD3.GPIO_Label=TTL1
PD3.Signal=GPXTI3
PD4.GPIOParameters=GPIO_Label
PD4.GPIO_Label=TTL2
PD4.Signal=GPXTI4
PD5.GPIOParameters=GPIO_Label
PD5.GPIO_Label=TTL3
PD5.Signal=GPXTI5
PD6.GPIOParameters=GPIO_Label
PD6.GPIO_Label=TTL4
PD6.Signal=GPIO_Output
PD7.GPIOParameters=GPIO_Label
PD7.GPIO_Label=TTL5
PD7.Signal=GPIO_Output
PD8.GPIOParameters=GPIO_Label
PD8.GPIO_Label=STLINK_TX
PD8.Mode=Asynchronous
PD8.Signal=USART3_TX
PD9.GPIOParameters=GPIO_Label
PD9.GPIO_Label=STLINK_TX
PD9.Mode=Asynchronous
PD9.Signal=USART3_RX
PE0.GPIOParameters=GPIO_Label
PE0.GPIO_Label=DAT7_OUT
PE0.Signal=GPIO_Output
PE1.GPIOParameters=GPIO_Label
PE1.GPIO_Label=DAT7
PE1.Signal=GPIO_Input
PE10.GPIOParameters=GPIO_Label
PE10.GPIO_Label=iDIV2_S0
PE10.Signal=GPIO_Output
PE11.GPIOParameters=GPIO_Label
PE11.GPIO_Label=iDIV1_S2
PE11.Signal=GPIO_Output
PE12.GPIOParameters=GPIO_Label
PE12.GPIO_Label=iDIV1_S1
PE12.Signal=GPIO_Output
PE13.GPIOParameters=GPIO_Label
PE13.GPIO_Label=iDIV1_S0
PE13.Signal=GPIO_Output
PE14.GPIOParameters=GPIO_Label
PE14.GPIO_Label=CEN
PE14.Signal=GPIO_Output
PE15.GPIOParameters=GPIO_Label
PE15.GPIO_Label=UPSAT
PE15.Signal=GPXTI15
PE2.GPIOParameters=GPIO_Label
PE2.GPIO_Label=SPI_SCK
PE2.Mode=Full_Duplex_Slave
PE2.Signal=SPI4_SCK
PE3.GPIOParameters=GPIO_Label
PE3.GPIO_Label=SCK_OUT
PE3.Signal=GPIO_Output
PE4.GPIOParameters=GPIO_Label
PE4.GPIO_Label=SPI_NSS
PE4.Mode=NSS_Signal_Hard_Input
PE4.Signal=SPI4_NSS
PE5.GPIOParameters=GPIO_Label
PE5.GPIO_Label=SPI_MISO
PE5.Mode=Full_Duplex_Slave
PE5.Signal=SPI4_MISO
PE6.GPIOParameters=GPIO_Label
PE6.GPIO_Label=SPI_MOSI
PE6.Mode=Full_Duplex_Slave
PE6.Signal=SPI4_MOSI
PE8.GPIOParameters=GPIO_Label
PE8.GPIO_Label=iDIV2_S1
PE8.Signal=GPIO_Output
PE9.GPIOParameters=GPIO_Label
PE9.GPIO_Label=iDIV2_S2
PE9.Signal=GPIO_Output
PH0-OSC_IN\ (PH0).Mode=HSE-External-Clock-Source
PH0-OSC_IN\ (PH0).Signal=RCC_OSC_IN
RCC.HSE_VALUE=10000000
RCC.SYSCLKFreq_VALUE=75000000
RCC.SYSCLKSource=RCC_SYSCLKSOURCE_PLLCLK
board=custom

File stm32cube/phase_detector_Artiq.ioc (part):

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Mcu.Name=STM32H743VITx
Mcu.Package=LQFP100
Mcu.UserName=STM32H743VITx
PA0.GPIOParameters=GPIO_Speed,GPIO_Label
PA0.GPIO_Label=XREF
PA0.GPIO_Speed=GPIO_SPEED_FREQ_VERY_HIGH
PA0.Signal=S_TIM2_CH1_ETR
PA10.GPIOParameters=GPIO_Label
PA10.GPIO_Label=RXD1
PA10.Mode=Asynchronous
PA10.Signal=USART1_RX
PA11.Mode=Asynchronous
PA11.Signal=UART4_RX
PA12.Mode=Asynchronous
PA12.Signal=UART4_TX
PA13\ (JTMS/SWDIO).Mode=JTAG_4_pins
PA13\ (JTMS/SWDIO).Signal=DEBUG_JTMS-SWDIO
PA14\ (JTCK/SWCLK).Mode=JTAG_4_pins
PA14\ (JTCK/SWCLK).Signal=DEBUG_JTCK-SWCLK
PA15\ (JTDI).Mode=JTAG_4_pins
PA15\ (JTDI).Signal=DEBUG_JTDI
PA4.GPIOParameters=GPIO_Label
PA4.GPIO_Label=XVCO
PA4.Signal=S_TIM5_ETR
PA9.GPIOParameters=GPIO_Label
PA9.GPIO_Label=TXD1
PA9.Mode=Asynchronous
PA9.Signal=USART1_TX
PB12.GPIOParameters=GPIO_Label
PB12.GPIO_Label=PHDET_NSS
PB12.Signal=GPIO_Output
PB13.GPIOParameters=GPIO_Label
PB13.GPIO_Label=PHDET_SCK
PB13.Mode=Full_Duplex_Master
PB13.Signal=SPI2_SCK
PB3\ (JTDO/TRACESWO).Mode=JTAG_4_pins
PB3\ (JTDO/TRACESWO).Signal=DEBUG_JTDO-SWO
PC1.GPIOParameters=GPIO_Label
PC1.GPIO_Label=PHDET_MOSI
PC1.Mode=Full_Duplex_Master
PC1.Signal=SPI2_MOSI
PC2_C.GPIOParameters=GPIO_Label
PC2_C.GPIO_Label=PHDET_MISO
PC2_C.Mode=Full_Duplex_Master
PC2_C.Signal=SPI2_MISO
PC6.GPIOParameters=GPIO_Label
PC6.GPIO_Label=TXD2
PC6.Mode=Asynchronous
PC6.Signal=USART6_TX
PC7.GPIOParameters=GPIO_Label
PC7.GPIO_Label=RXD2
PC7.Mode=Asynchronous
PC7.Signal=USART6_RX
PD8.GPIOParameters=GPIO_Label
PD8.GPIO_Label=STLINK_RX
PD8.Mode=Asynchronous
PD8.Signal=USART3_TX
PD9.GPIOParameters=GPIO_Label
PD9.GPIO_Label=STLINK_TX
PD9.Mode=Asynchronous
PD9.Signal=USART3_RX
PE10.GPIOParameters=PinState,GPIO_PuPd,GPIO_Label
PE10.GPIO_Label=DIV2_S0
PE10.GPIO_PuPd=GPIO_PULLDOWN
PE10.PinState=GPIO_PIN_SET
PE10.Signal=GPIO_Output
PE11.GPIOParameters=PinState,GPIO_PuPd,GPIO_Label
PE11.GPIO_Label=DIV1_S2
PE11.GPIO_PuPd=GPIO_PULLDOWN
PE11.PinState=GPIO_PIN_SET
PE11.Signal=GPIO_Output
PE12.GPIOParameters=PinState,GPIO_PuPd,GPIO_Label
PE12.GPIO_Label=DIV1_S1
PE12.GPIO_PuPd=GPIO_PULLDOWN
PE12.PinState=GPIO_PIN_SET
PE12.Signal=GPIO_Output
PE13.GPIOParameters=PinState,GPIO_PuPd,GPIO_Label
PE13.GPIO_Label=DIV1_S0
PE13.GPIO_PuPd=GPIO_PULLDOWN
PE13.PinState=GPIO_PIN_SET
PE13.Signal=GPIO_Output
PE14.GPIOParameters=PinState,GPIO_PuPd,GPIO_Label
PE14.GPIO_Label=PHDET_CEN
PE14.GPIO_PuPd=GPIO_PULLUP
PE14.PinState=GPIO_PIN_SET
PE14.Signal=GPIO_Output
PE8.GPIOParameters=PinState,GPIO_PuPd,GPIO_Label
PE8.GPIO_Label=DIV2_S1
PE8.GPIO_PuPd=GPIO_PULLDOWN
PE8.PinState=GPIO_PIN_SET
PE8.Signal=GPIO_Output
PE9.GPIOParameters=PinState,GPIO_PuPd,GPIO_Label
PE9.GPIO_Label=DIV2_S2
PE9.GPIO_PuPd=GPIO_PULLDOWN
PE9.PinState=GPIO_PIN_SET
PE9.Signal=GPIO_Output
PH0-OSC_IN\ (PH0).Mode=HSE-External-Oscillator
PH0-OSC_IN\ (PH0).Signal=RCC_OSC_IN
PH1-OSC_OUT\ (PH1).Mode=HSE-External-Oscillator
PH1-OSC_OUT\ (PH1).Signal=RCC_OSC_OUT
RCC.HSE_VALUE=10000000
RCC.SYSCLKFreq_VALUE=75000000
RCC.SYSCLKSource=RCC_SYSCLKSOURCE_PLLCLK
board=NUCLEO-H743ZI2

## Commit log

2024-11-03 importing nucleo eth template
2024-11-03 adding kicad project
2024-11-13 try to write read registers, not wirking yet
2024-11-13 uc-phd communication works
2025-10-01 some initial commits
2025-10-01 new kicad project
2025-10-01 pull-down on div pins
2025-10-01 setdiv created
2025-10-05 running ref counter, not precise yet
2025-10-22 kicad, no changes, just opening
2025-10-22 phdet spi config
2025-10-28 preparation for lfphdet - not ready
2025-10-28 reading - not working yet
2025-11-04 write read reg works
2025-12-01 some tests with timer etc
2025-12-01 remove cube old project
2025-12-01 acknowledgements
